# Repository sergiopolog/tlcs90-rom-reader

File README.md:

# TLCS-90 Internal ROM Reader Tool

TLCS-90 ROM Reader is custom made tool intended to read the inner ROM content that TLCS-90 series Toshiba MCUs have internally, at least for the models which support it.

[](img/mcu-nmk215.jpeg)

Devices in the TLCS-90 family from Toshiba are MCUs with a Z80 core and a quite similar instruction set, but they have additional features than the original CPU from Zilog, such us:
  - Internal Counters
  - Wathdog
  - A/D converters
  - Serial port support
  - Stepping motors support
  - and more...
  
There are also devices in the family which have some space reserved for Internal ROM and RAM in their memory map, allowing to have an entire microcomputer system in a single chip (program code and work RAM could be included inside the chip).

## Where it started

Motivation of doing this started some years ago when I sourced a pcb of the GunNail arcade game from NMK (1992) in a very bad condition, including lot of rust and rotten components and traces.
Some the chips included in that pcb were very clearly faulty, with broken legs and serious damage. One of them is labeled as NMK-215, a supposedly custom-chip made by NMK back then with custom behavior, as its name already says.
After some investigation, I realized that component is in fact a Toshiba MCU, because the pinout matches with one of the models of those series as shown on their databook, at least the power pins (Vcc and Ground), reset, clock, address and data buses.
Those types of MCU, as said above, could have internal ROM, where it stores a program to be executed by the MCU itself. And that's probably the case for that NMK board.

Then, the first attempt to read if the internal ROM was in a phisical way. I sent the chip to [Furrtek](http://furrtek.free.fr) a while back to be decapped and, in a luckly chance, the ROM could be optically reed from the die, but there was no luck on that shot. The die reveals no visible ROM area, at least from the top view, ~~and a delayering (quite more complex method) should be performed to check if the ROM area will be visible underneath the top metal layer.~~ -> Thanks to [Travis Goodspeed](https://x.com/travisgoodspeed) for pointing out that TLCS-47 series has _Implant ROM_ (Toshiba most likely used the same technology for newer TLCS-90 series) meaning that the difference between P and N silicon describes the bit and, in fact, it's not optically visible  even after delayering, because they are the exact same color.

So, after that try, the next efforts were spent on trying to find a way to exploit the device and read the contents from outside using some external process,  like the way some other MCU devices were successfully dumped.

And that's how this project started. After 3 diferent revisions of the pcb and software made during the process in order to know how the MCU behaves in different scenarios and many of its features, it works for a good number of devices tested by now.

The internal ROMs dumped from several devices helped in improving and even managing to complete emulation on some games in MAME.

## TLCS-90 Series MCUs

| ROM | RAM | CMOS MASK ROM MCU | CMOS NO ROM | PROM MCU   | RESET PIN | SUPPORTED BY THE READER |
| --- | --- | ----------------- | ----------- | ---------- | --------- | --------- |
|  -  |  -  |  -                | TMP90C041N  |  -         | 22        | (not needed) |
|  -  |  1K |  -                | TMP90C141N  |  -         | 22        | (not needed) |
| 4K  | 128 | TMP90C400N        | TMP90C401N  | TMP90P800N | 35        | YES (using adapter) |
| 8K  | 256 | TMP90C800N        | TMP90C801N  | TMP90P800N | 35        | YES (using adapter) |
| **8K**  | **256** | **TMP90C840AN**       | **TMP90C841AN** | **TMP91P640N** | **22**        | **YES**   |
| 8K  | 256 | TMP90C844AN       | TMP90C845AN | TMP90PH44N | 47        | NO        |
| 16K | 320 | TMP91C642AN       | -           | TMP91P642N | 46        | NO        |
| **16K** | **512** | **TMP91C640N**        | **TMP91C641N**  | **TMP91P640N** | **22**        | **YES**   |
| 16k | 512 | TMP90CH44N        | TMP90CH45N  | TMP90PH44N | 47        | NO        |
| **32K** | **1K**  | **TMP90CM40AN**       | **TMP90C141N**  | **TMP90PM40N** | **22**        | **YES** (not tested yet)  |

**Bold** ones have the same pinout as NMK-215.
Not supported ones have slighty different architecture, lacking of /NMI pin, making the Reader pcb not able to achieve the process.
The 400N and 800N ones are (theoretically) supported but a pinout adapter is needed to use them with Reader PCB. However, that is currently untested yet, as I couldn't source any device of those models to check them out.

The tool consists in a combination of a custom-made pcb, a program code written to be executed on the targeted MCU itself, a PLD and glue logic to make all things work together. The tool runs by itself without needing to attach it to another hardware or so, it only requires to be populated with the proper components and powered it using +5V. 

## DISCLAIMER
Any use of this project is under **your own responsibility**. **You** will be responsible of checking the proper installation and functionality of your board and the compatiblity of the chips **You** will insert into it. By using this project **You** will agree that I cannot be held responsible if it will destroy any of your devices, burn down your house or whatever.

Do **NOT** come to me for hand-holding using this. It is **NOT** a plug-and-play tool, and it is something I created for my own research and use, and I released in case someone might have an use for it.

## Assemble

All components used on the PCB design are "Through-Hole". That makes the assembly easier.

1. Build the pcb using the gerbers located in the [pcb/gerbers](pcb/gerbers) folder.
2. Burn the program code from the binary file located at [src](src) folder into a 27C512 EPROM.
3. Burn the PLD from the jedec file located at [pld](pld) folder into a GAL22V10 device.
4. Install all the components into the pcb. Sockets are recommended at least for MCU, EPROM, EEPROM and PLD devices. There is an interactive, html-based BOM file located at [pcb/bom](pcb/bom) which is useful when populating the board.

## How to use

> **IMPORTANT:** Ensure that device is one of the compatible models marked above before proceeding with the process. If the model is unknown, you can check if it is one of the directly supported models by checking the following things:
> * Pins 1 and 64 should be tied to Vcc in the original pcb where it was installed.
> * Pins 2 and 32 should be tied to GND in the original pcb where it was installed.
> * Pin 55 should be tied to Vcc (or to a pull-up resistor) if it uses internal ROM.
> * Additionally, Pin 21 could be tied to Vcc aswell, indicating that no external interrupt is used. However this doesn't happen always.

First of all, ensure the 28C256 EEPROM is unprotected. This type of device can be protected making that any write performed on the device will be rejected. So, you need to ensure always to "Off Protect" the device before installing it on the board. Don't do any other actions on the EEPROM other than de-protecting it before inserting it in the socket of the reader PCB. (Thanks **kuze** for discovering and testing this)

1. Set the `DSW2` with an initial value of **4** (0100).
2. Select the internal ROM size of the target device using `DSW1`. If device model is unknown, then select 32K option to perform a full read. Perhaps, some space should be discarded after reading process.
3. Set the `/EA` switch to the left position **(ON)** (external mode)
4. Turn the power on. There are two options for powering the board:
	- Via Mini-molex floppy drive connector directly from an ATX PSU or similar. In this case connect only the power connector to `J1` and use the `SW1` **only** to turn on the board. Ensure that left pin is +5V and two middle pins are GND. This is the standard pinout for this kind of connectors.
	- Via Barrel connector (**Tip Positive - Ring Negative!!**) up to 12V from an external PSU. In this case connect only the barrel connector to `J2` and use the `SW2` **only** to turn on the board. (It works fine with 9V and 12V external power supplies, but in case of 12V, installing a heatsink on `U15` - L7805 is highly recommended)
5. Push the `/RESET` button shortly and green LED at `D2` will turn on, marking the PCB is ready.
6. Toggle the `/EA` switch to the right position **(OFF)** (internal mode)
7. Push again the `/RESET` button to start the read process. Green LED turns off.
8. When green LED turns on again, the process ended successfully. Time spent in the read process depends on the MCU model and the size of its internal ROM. A 8K internal ROM takes about 55 seconds, 16K one about 110 seconds and 32K one about 220 seconds using a 4MHz XTAL on the PCB. It could be upgraded up to 10MHz (max freq. allowed by the MCU), in order to reduce those dump times, but that's not really needed.
9. The contents of the internal ROM are written to the EEPROM located at `U3`. Carefully extract it from the socket and read contents with a proper EPROM reader.

If the initial rom size was unknown and the model wasn't really a 32K device, some extra content was read by the process and was placed at the end of the dumped file. In that file could be some flag values at some specific addresses marking what is the real internal ROM size:
* If a **"3B"** value is located at `$2000`, then the internal ROM is only  8K an the content between `$2000 - $8000` in the dump file should be discarded.
* If a **"4B"** value is located at `$4000`, then the internal ROM is only 16K an the content between `$4000 - $8000` in the dump file should be discarded.
* If none of those values are present at those positions, then the dump is really 32K length and no content should be discarded.

> **NOTE:** If the green led doesn't turn on long after those estimated times, then it should be a problem in the read process. Please check the [Special cases](#special-cases) section.

Powering the board using Barrel Connector and an external 9V DC power supply (**Tip Positive!**):  
[](img/Powered_by_Barrel_Connector.jpeg)

## How it works

### TLCS-90 features

The dump method implemented in this tool sits over these features/behaviors of the TCLS-90 MCUs:

* The MCU provides an input pin called `/EA` ("External Access") and when it's asserted (low level), the MCU ignores the internal ROM (and RAM) space and addresess it to the outside using the address port pins. When it's not asserted it uses the internal ROM placed on the beginning of the memory map ($0000 - $2000, $0000 - $4000.. etc, depending of the specific MCU model). So we can externally control if the MCU starts in external or internal mode.
* The `/EA` pin doesn't allow a hot-swap, when the MCU is running, and only sets the value when resetting the device.
* Like a plain Z80 cpu, the first instruction fetched after reset is on `$0000` address. If the internal mode is enabled, that fetch is done from the internal ROM.
* Reset process only clear values for a few registers in the MCU. These are the PC register, AF register pair and IFF flags. The rest of the registers remain unchanged from previous execution (if any), including SP (Stack Pointer)
* When resetting the device in internal mode, the Address pins are set as input port by default, and it should be configured as address pins programatically if desire.
* External interrupt handling is basically the same as a plain Z80, saving PC value and AF value into the stack and restore them after ending interrupt subroutine.

### Exploit

Considering that, this is basically how the dump method works:

1. Start the device in external mode and the program code puts an external address value into the Stack Point register (SP). Then, the program halt the device waiting for reset.
2. Manually toggle the /EA pin to switch to internal mode and then reset again.
3. As SP value remains unchanged after that reset, if any interrupt is asserted, the device will store the PC value and some others into the stack, that is currently now at external zone pointed by the previous SP value
4. Inmediatly right after that second reset is released, the pcb logic generates a pulse into the `/NMI` pin to send an (non-maskable) interrupt. The device doesn't have enough time to fetch firsts instructions at `$0000` (that would probably set the SP to its own value), and it goes to handle the interrupt.
5. Device stores the PC and other values into the stack, that is currently on external zone, but the Address Port is configured as input port right after reset, so it doesn't effectively output the address on the device address pins to store those values, but doesn't care, they will not be used.
6. After running the interrupt subroutine (tipycally, it simply returns the control without doing anything else related to outside), the PC value (and others) need to be returned back from stack, and the device tries to read them from the external zone.
7. The pcb logic, using the `/RD` pin to count each fetch, artificially sends a new convenient PC value, so now the PC in the device is pointing to the zone we want (external zone).
8. The device tries to fetch instruction from the new injected PC address value, but the Address Port still remains as an input port after reset, so it doesn't output the proper address value to fetch the instruction.
9. The pcb logic again, using the `/RD` pin to count the subsequent fetches, artificially sends a sequence of 6 bytes, conforming 2 instructions to be executed by the device. Those instructions were carefully chosen to enable the Address pin to act effectively as an address port (output).
10. Next instruction is fetched normally by the device using the address port on the next PC value, and then we finally gain control of the device.
11. Next step is initiallize the rest of the device registers and ports and run the custom program stored in the external EPROM
12. The MCU itself copies the internal rom content ($0000 to $1FFF, or to $3FFF, or to $7FFF) to the EEPROM (Non-volatile) installed in the PCB by running the program code in the EPROM.

### Attack Timing

Below picture shows the main signals involved in the attack and how they evolve during the attack process:

[](img/tlcs90-attack-timing.jpg)

### Special cases

If the interrupt routine does one or more reads by addressing the external zone, prior to return the control, or it pushes/pops values from the stack during that interrupt subroutine (the stacks pointer still points to the external zone and it provokes writes/reads there), the counter on the PCB will be confused and won't inject the proper values at the proper times. So if the internal code does that, this method will not work with the initial configuration. Anyway, it's rare that the NMI routine does data fetches from the external zone.

In this case, a workaround could be effective. That is trying to locate where the interrupt subroutine ends and what is the first fetch from stack during RETI instruction to take the AF register and then PC register. By adjusting DSW2, substracting some units to the initial configured value, will delay the reads count in order to sync the time when RETI tries to fetch PC value from stack with the time the PCB logic injects it to the data bus (i.e.: 4 -> 2).

Another rare case that could happen is that RET instruction is used instead of RETI when ending the interrupt subroutine. The difference is that RET only does "POP PC" and RETI does both "POP AF" and then "POP PC", so there will be two less read cycles when returning from interrupt. That could be adjusted with the DSW2 by adding two units to the value configured there (i.e.: 4 -> 6) in order to sync the time when PC value is injected in the same way as the previous case.

In all of these rare cases, the way to go is playing with different values on the DSW2, by adding or substracting some units to the value configured in it until syncing the time when the new PC value should be injected.

Obviously, if the interrupt routine does many complex things, a custom solution should be made for attacking that specific device. A Logic Analyzer would be a great help to inspect what happens after the NMI pulse is generated by the reader PCB logic.

In a weird case, I discovered that one program has a direct jump on the interrupt subroutine, instead of the RETI instruction. In that case, the program jumped to remote program address (inside internal ROM) and continue executing instructions, until it calls to a subroutine. In that moment the value of the PC was stored in the stack (still pointing to external zone) and when the subroutine ended, the program tried to take the PC value back from the stack and at that point the new PC value was injected. In all of that execution time, no external fetches were done, so the first one was for returing back that PC value, and the new one was injected.

## Known TLCS-90 based devices

Below there is a table with the current known devices based on TLCS-90 series MCUs, model, features and if the contents are currently dumped, aswell.

|  Device Ref.  |  Device Model  |  Package  |  Dev. Company  |  Found on Hw  |  Dumped?  |  Config. used to dump (DSW2)  | Picture |
| --- | --- | ----------------- | ----------------- | ----------- | ----------- | ----------- | ----------- |
|  NMK-004  |  TMP90840  |  QFP64  |  NMK  |  many NMK games (sound cpu)  |  [**Yes**](https://github.com/mamedev/mame/blob/0006fba49565386afa9b66d9fb8e02f744cf7cdb/src/mame/nmk/nmk004.cpp#L83)<br/>(using [trap15 method](http://daifukkat.su/blog/archives/2014/09/13/nmk004_rom_dumping_part_5_the_release/))<br/>Also dumped using **TLCS90-ROM-Reader** and adapter located at [adapter/tmp90c840-qfc2sdip](adapter/tmp90c840-qfc2sdip)  |  2  |  [Link](img/mcu-nmk004.jpeg)  |
|  NMK-110  |  TMP91640  |  SDIP64  |  NMK  |  ddealer & tdragon<br/>(different internal ROM on each one)  |  [**Yes**](https://github.com/mamedev/mame/blob/0006fba49565386afa9b66d9fb8e02f744cf7cdb/src/mame/nmk/ddealer.cpp#L463)  and  [**Yes**](https://github.com/mamedev/mame/blob/0006fba49565386afa9b66d9fb8e02f744cf7cdb/src/mame/nmk/nmk16.cpp#L6447)  |  4  |  [Link](img/mcu-nmk110.jpeg)  |
|  NMK-113  |  TMP91640  |  SDIP64  |  NMK  |  hachamf  |  [**Yes**](https://github.com/mamedev/mame/blob/0006fba49565386afa9b66d9fb8e02f744cf7cdb/src/mame/nmk/nmk16.cpp#L6801)  |  4  |  [Link](img/mcu-nmk113.jpeg)   |
|  NMK-215  |  TMP90840  |  SDIP64  |  NMK  |  sabotenb, bjtwin, macross, gunnail  |  [**Yes**](https://github.com/mamedev/mame/blob/0006fba49565386afa9b66d9fb8e02f744cf7cdb/src/mame/nmk/nmk16.cpp#L7480)  |  4  |  [Link](img/mcu-nmk215.jpeg)   |
|  -  |  TMP90840  |  SDIP64  |  Dynax  |  mjvegas  |  [**Yes**](https://github.com/mamedev/mame/blob/26072bb747281a3abb519dc2a2c38884b9c5d479/src/mame/dynax/royalmah.cpp#L5159)  |  2  |  [Link](img/mcu-mjvegas.jpeg)   |
|  -  |  TMP90840  |  SDIP64  |  Dynax  |  cafedoll  |  [**Yes**](https://github.com/mamedev/mame/blob/26072bb747281a3abb519dc2a2c38884b9c5d479/src/mame/dynax/royalmah.cpp#L5042)  |  2  |  [Link](img/mcu-cafedoll.jpeg)  |
|  -  |  TMP90840  |  SDIP64  |  Dynax  |  cafetime  |  [**Yes**](https://github.com/mamedev/mame/blob/26072bb747281a3abb519dc2a2c38884b9c5d479/src/mame/dynax/royalmah.cpp#L98)  |  2  |  [Link](img/mcu-cafetime.jpeg)  |
|  -  |  TMP91640  |  SDIP64  |  Dynax  |  cafebrk  |  [**Yes**](https://github.com/mamedev/mame/blob/26072bb747281a3abb519dc2a2c38884b9c5d479/src/mame/dynax/royalmah.cpp#L5340)  |  2  |  [Link](img/mcu-cafebrk.jpeg)  |
|  -  |  TMP91640  |  SDIP64  |  Dynax  |  cafepara |  [**Yes**](https://github.com/mamedev/mame/blob/26072bb747281a3abb519dc2a2c38884b9c5d479/src/mame/dynax/royalmah.cpp#L5072)  |  2  |  [Link](img/mcu-cafepara.jpeg)  |
|  -  |  TMP90840  |  SDIP64  |  Dynax  |  mjtensin  |  [**Yes**](https://github.com/mamedev/mame/blob/fe923e9b3c464d7e373dd1992c6001b47b572e19/src/mame/dynax/royalmah.cpp#L4868)<br/>*(not used by the game code)*  |  4  |  [Link](img/mcu-mjtensin.jpeg)  |
|  -  |  TMP91640  |  SDIP64  |  Dynax  |  majrjh  |  [**Yes**](https://github.com/mamedev/mame/blob/000c31fae55296ae3a853f2ffbe44a6d46dc7a3a/src/mame/dynax/royalmah.cpp#L4970)  |  2  |  [Link](img/mcu-majrjhdx.jpeg)  |
|  -  |  TMP91640  |  SDIP64  |  Dynax  |  majrjhdx  |  [**Yes**](https://github.com/mamedev/mame/blob/000c31fae55296ae3a853f2ffbe44a6d46dc7a3a/src/mame/dynax/royalmah.cpp#L4955)<br/>*(same dump as majrjh)*  |  2  |  [Link](img/mcu-majrjhdx.jpeg)  |
|  -  |  ?  |  SDIP64  |  Dynax  |  gekisha  |  No  |  -  |  -  |
|  -  |  TMP91640  |  SDIP64  |  Dynax  |  tenkai  |  [**Yes**](https://github.com/mamedev/mame/blob/88a47305a4a5987fbe0e9160d8dd6b6a9c3a2314/src/mame/dynax/dynax.cpp#L6820)<br/>*(already dumped previosly)*<br/>*(pending to be dumped using this method)*  |  -  |  -  |
|  -  |  ?  |  SDIP64  |  Dynax  |  tenkai2b  |  No  |  -  |  -  |
|  -  |  TMP90840  |  SDIP64  |  Dynax  |  ougonhai  |  [**Yes**](https://github.com/mamedev/mame/blob/fe923e9b3c464d7e373dd1992c6001b47b572e19/src/mame/dynax/dynax.cpp#L7021)  |  2  |  [Link](img/mcu-ougonhai.jpeg)   |
|  -  |  TMP90840  |  SDIP64  |  Dynax  |  mjreach  |  [**Yes**](https://github.com/mamedev/mame/blob/fe923e9b3c464d7e373dd1992c6001b47b572e19/src/mame/dynax/dynax.cpp#L6662)  |  2  |  [Link](img/mcu-mjreach.jpeg)   |
|  -  |  TMP90840  |  SDIP64  |  Dynax  |  mjreach2  |  [**Yes**](https://github.com/mamedev/mame/blob/3f9d6b905f18b8800a9420abdd981ee51502d85e/src/mame/dynax/dynax.cpp#L6751)  |  2  |  [Link](img/mcu-mjreach2.jpeg)   |
|  -  |  ?  |  SDIP64  |  Jaleco  |  avspirit  |  No  |  -  |  -  |
|  -  |  TMP91640  |  SDIP64  |  Jaleco  |  edf  |  [**Yes**](https://github.com/mamedev/mame/blob/df3e2de8e1815f0c22419c298471fbb8776858a2/src/mame/jaleco/megasys1.cpp#L3145)<br/>Thanks to **Darren Olafson**<br/>Double checked by *me*.  |  6  |  [Link](img/mcu-edf.jpeg)  |
|  MO-91009  |  TMP91640  |  SDIP64  |  Jaleco  |  64street  |  [**Yes**](https://github.com/mamedev/mame/blob/7b047641fe763667882a8c3320ad24163c63d327/src/mame/jaleco/megasys1.cpp#L2297)  |  6  |  [Link](img/mcu-mo91009.jpeg)  |
|  MO-91021  |  TMP91640  |  SDIP64  |  Jaleco  |  bigstrik  |  [**Yes**](https://github.com/mamedev/mame/blob/7b047641fe763667882a8c3320ad24163c63d327/src/mame/jaleco/megasys1.cpp#L2879)  |  6  |  [Link](img/mcu-mo91021.jpeg)  |
|  MO-91028  |  TMP91640  |  SDIP64  |  Jaleco  |  chimerab |   [**Yes**](https://github.com/mamedev/mame/blob/7b047641fe763667882a8c3320ad24163c63d327/src/mame/jaleco/megasys1.cpp#L2927)<br/>*(same dump as cybattlr)*<br/>Thanks to **kuze**  |  6  |  [Link](img/mcu-mo91028.jpeg)  |
|  -  |  ?  |  SDIP64  |  Jaleco  |  chimeraba |  No  |  -  |  -  |
|  MO-91028  |  TMP91640  |  SDIP64  |  Jaleco  |  cybattlr  |   [**Yes**](https://github.com/mamedev/mame/blob/7b047641fe763667882a8c3320ad24163c63d327/src/mame/jaleco/megasys1.cpp#L3049)<br/>Thanks to **kuze**  |  6  |  [Link](img/mcu-mo91028.jpeg)  |
|  MO-91044  |  ?  |  SDIP64  |  Jaleco  |  hayaosi1  |  No  |  -  |  -  |
|  MO-92033  |  TMP91640  |  SDIP64  |  Jaleco  |  peekaboo  |  [**Yes**](https://github.com/mamedev/mame/blob/225c0586cb9f0f3c8fb234736ba2863dffa12c69/src/mame/jaleco/megasys1.cpp#L4424)  |  4  |  [Link](img/mcu-mo92033.jpeg)  |
|  -  |  TMP90840  |  QFP64  |  Toshiba  |  T1600 Laptop PSU  |  [**Yes**](bin/mcu-t1600psu.bin)<br/>Using adapter located at [adapter/tmp90c840-qfc2sdip](adapter/tmp90c840-qfc2sdip)  |  4  |  [Link](img/mcu-t1600psu.jpeg)  |

If you find more devices based on this MCU series, have additional info or successfully dump some, please let me know to add them to the above table, just as reference. 

## Prototypes and previous versions

During the process some previous versions of the board was manufactured and tested, in order to understand the behaviour of the MCU in some special cases and test different attacks over it. 

### Version 1 (Proto - Test board)

This board was the first ever made and the purpose of that was testing the behaviour of the TLCS90 devices and perform some simple attack attempts and see how the device behaves under them.

[](img/TLCS90-rom-reader-v1.jpg)

### Version 2 (Proto - Attack board)

Using the data compiled from the first version, the second one includes the implementation of the main attack with some small variants to be tested with real devices.

[](img/TLCS90-rom-reader-v2-front.jpg)

Multiple patches needed to be done directly in the pcb in order to fix errors and test slight variations of the attack :D

[](img/TLCS90-rom-reader-v2-back.jpeg)

### Version 3 (Final version)

After confirming the attack is successfull for several devices, the unused parts were removed and the layout was simplified. Added support for selecting the type of device (by its internal ROM size). Also an additional option to power the board via barrel connector was added. 

[](img/mcu-nmk215.jpeg)

## Special Thanks

Special thanks to  [hammy](https://www.youtube.com/@HammyArcade) for his valuable help on the research of this project and helping in sourcing PCBs and TLCS90 devices for testing.

## Contact

[@Recre_Piscis](https://x.com/Recre_Piscis) on X (_Twitter_).

## License

See [LICENSE](LICENSE) for more details.

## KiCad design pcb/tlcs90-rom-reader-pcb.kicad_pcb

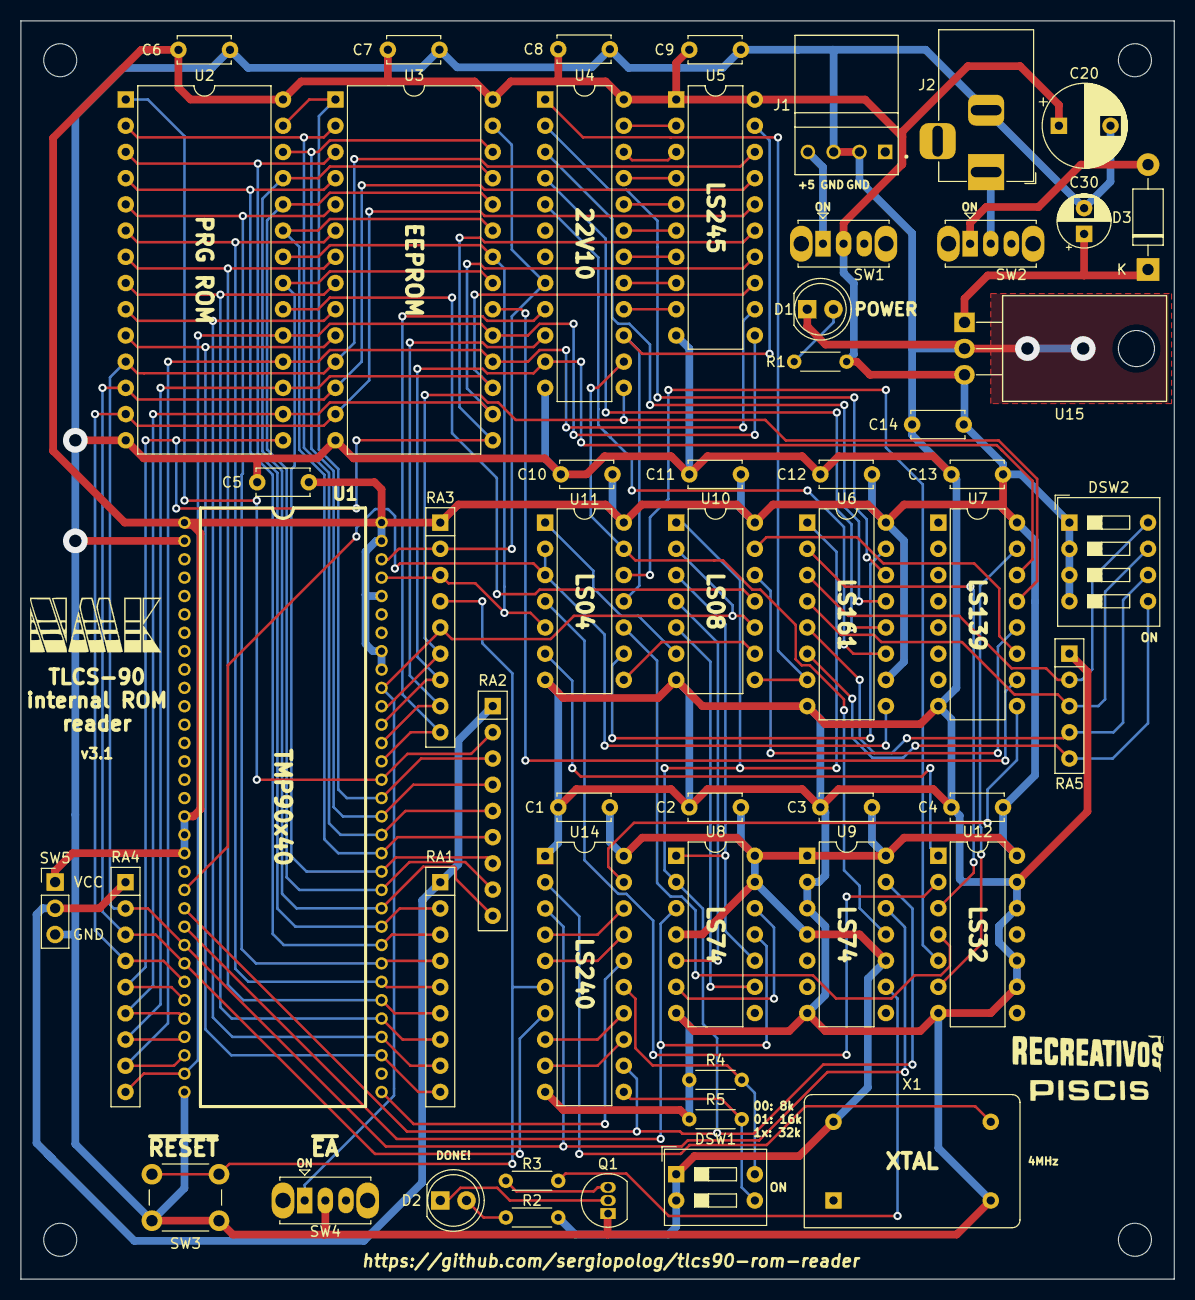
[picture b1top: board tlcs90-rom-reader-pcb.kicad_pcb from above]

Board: 2 copper layers, 111.8 x 121.9 mm, 60 parts (0 on the bottom side), 92 nets.

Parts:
C1, C2, C3, C4, C5, C6, C7, C8, C9, C10, C11, C12, C13, C14: 0.1; C_Disc_D5.0mm_W2.5mm_P5.00mm
C20: 470u 16V; CP_Radial_D8.0mm_P5.00mm
C30: 0.22; CP_Radial_D5.0mm_P2.50mm
D1: RED LED; LED_D5.0mm
D2: GREEN LED; LED_D5.0mm
D3: 1N4001; D_DO-41_SOD81_P10.16mm_Horizontal
DSW1: SW_DIP_x02; SW_DIP_SPSTx02_Slide_9.78x7.26mm_W7.62mm_P2.54mm
DSW2: SW_DIP_x04; SW_DIP_SPSTx04_Slide_9.78x12.34mm_W7.62mm_P2.54mm
H1, H2, H3, H4: MountingHole; MountingHole_3.2mm_M3
J1: Conn_01x04; TE_171826-4
J2: Conn_Coaxial_Power; BarrelJack_Horizontal
L1: RECRE-PISCIS-LOGO-10mm; recre_piscis_logo
L2: NMK-LOGO; nmk-logo
Q1: Q_NPN_ECB; TO-92_Inline
R1, R3: 4.7K; R_Axial_DIN0204_L3.6mm_D1.6mm_P5.08mm_Horizontal
R2: 330; R_Axial_DIN0204_L3.6mm_D1.6mm_P5.08mm_Horizontal
R4, R5: 10K; R_Axial_DIN0204_L3.6mm_D1.6mm_P5.08mm_Horizontal
RA1, RA2, RA3, RA4: 10K; R_Array_SIP9
RA5: 10K; R_Array_SIP5
SW1, SW2, SW4: SW_SPDT; SW_Slide_1P2T_CK_OS102011MS2Q
SW3: SW_Push; SW_PUSH_6mm
SW5: PinHeader; PinHeader_1x03_P2.54mm_Vertical
U1: TMP90C840AN; SDIP-64_W19.05mm
U2: 27C512; DIP-28_W15.24mm
U3: 28C256; DIP-28_W15.24mm
U4: GAL22V10; DIP-24_W7.62mm
U5: 74LS245; DIP-20_W7.62mm
U6: 74LS161; DIP-16_W7.62mm
U7: 74LS139; DIP-16_W7.62mm
U8, U9: 74LS74; DIP-14_W7.62mm
U10: 74LS08; DIP-14_W7.62mm
U11: 74LS04; DIP-14_W7.62mm
U12: 74LS32; DIP-14_W7.62mm
U14: 74LS240_Split; DIP-20_W7.62mm
U15: L7805; TO-220-3_Horizontal_TabDown
X1: 4MHz; Oscillator_DIP-14

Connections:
+12V: C30.1, D3.1, U15.1
/IN12V: J2.1, SW2.2
/SW12V: D3.2, SW2.1
A0: RA1.9, U1.35, U2.10, U3.10
A1: RA1.8, U1.36, U2.9, U3.9
A2: RA1.7, U1.37, U2.8, U3.8
A3: RA1.6, U1.38, U2.7, U3.7
A4: RA1.5, U1.39, U2.6, U3.6
A5: RA1.4, U1.40, U2.5, U3.5
A6: RA1.3, U1.41, U2.4, U3.4
A7: RA1.2, U1.42, U2.3, U3.3
A8: RA2.9, U1.43, U2.25, U3.25
A9: RA2.8, U1.44, U2.24, U3.24
A10: RA2.7, U1.45, U2.21, U3.21
A11: RA2.6, U1.46, U2.23, U3.23
A12: RA2.5, U1.47, U2.2, U3.2
A13: RA2.4, U1.48, U2.26, U3.26
A14: RA2.3, U1.49, U2.27, U3.1
A15: RA2.2, U1.50, U2.1
A16: RA3.9, U1.51, U4.9
A17: RA3.8, U1.52, U4.10
A18: RA3.7, U1.53, U4.11, U7.14
A19: RA3.6, U1.54, U4.13, U7.13
C0: U4.2, U6.14
C1: U4.3, U6.13
C2: U4.4, U6.12
C3: U4.5, U6.11
CLK: U1.23, U8.3, U8.11
D0: RA4.2, U1.24, U2.11, U3.11, U5.18, U9.12, U14.3
D1: RA4.3, U1.25, U2.12, U3.12, U5.17, U14.7
D2: RA4.4, U1.26, U2.13, U3.13, U5.16
D3: RA4.5, U1.27, U2.15, U3.15, U5.15
D4: RA4.6, U1.28, U2.16, U3.16, U5.14
D5: RA4.7, U1.29, U2.17, U3.17, U5.13
D6: RA4.8, U1.30, U2.18, U3.18, U5.12
D7: RA4.9, U1.31, U2.19, U3.19, U5.11
GND: C1.2, C2.2, C3.2, C4.2, C5.2, C6.2, C7.2, C8.2, C9.2, C10.2, C11.2, C12.2, C13.2, C14.2, C20.2, C30.2, D1.1, J1.2, J1.3, J2.2, Q1.1, R4.2, R5.2, RA5.1, SW3.2, SW4.2, SW5.3, U1.2, U1.32, U2.14, U3.14, U4.12, U5.10, U6.8, U7.8, U8.7, U9.2, U9.3, U9.7, U10.7, U11.7, U12.7, U12.9, U12.10, U12.12, U12.13, U14.1, U14.10, U15.2, X1.7
NMI-RESET-POS: U11.4, U12.2
unnamed: D1.2, R1.1
unnamed: D2.1, Q1.2
unnamed: D2.2, R2.1
unnamed: DSW1.3, R5.1, U14.11
unnamed: DSW1.4, R4.1, U14.15
unnamed: DSW2.5, RA5.5, U6.6
unnamed: DSW2.6, RA5.4, U6.5
unnamed: DSW2.7, RA5.3, U6.4
unnamed: DSW2.8, RA5.2, U6.3
unnamed: J1.4, SW1.1
unnamed: Q1.3, R3.1
unnamed: R3.2, U9.9
unnamed: RA1.1, RA2.1, RA4.1, SW5.2
unnamed: RA3.4, SW3.1, U14.6
unnamed: U1.33, U14.16
unnamed: U4.16, U5.9
unnamed: U4.17, U5.8
unnamed: U4.18, U5.7
unnamed: U4.19, U5.6
unnamed: U4.20, U5.5
unnamed: U4.21, U5.4
unnamed: U4.22, U5.3
unnamed: U4.23, U5.2
unnamed: U8.6, U8.12
unnamed: U8.1, U8.10, U10.3
unnamed: U8.5, U10.4
unnamed: U8.9, U10.5
unnamed: U10.6, U11.1
unnamed: U10.9, U11.8
unnamed: U7.12, U10.12
unnamed: U7.11, U10.13
unnamed: U11.6, U12.1
unnamed: U6.15, U11.9
unnamed: U11.10, U12.4
unnamed: U4.15, U5.19, U11.11
unnamed: U11.12, U12.5
unnamed: U4.14, U9.11, U11.13
unnamed: U6.2, U12.3
unnamed: U7.15, U12.6
unnamed: U14.2, X1.8
unnamed: U14.9, U14.13
unnamed: U14.8, U14.14
unnamed: U14.5, U14.17
unnamed: U14.4, U14.18
VCC: C1.1, C2.1, C3.1, C4.1, C5.1, C6.1, C7.1, C8.1, C9.1, C10.1, C11.1, C12.1, C13.1, C14.1, C20.1, DSW1.1, DSW1.2, DSW2.1, DSW2.2, DSW2.3, DSW2.4, R1.2, R2.2, RA3.1, SW1.2, SW5.1, U1.1, U1.17, U1.18, U1.19, U1.56, U1.57, U1.60, U1.63, U1.64, U2.28, U3.28, U4.24, U5.1, U5.20, U6.10, U6.16, U7.16, U8.4, U8.13, U8.14, U9.1, U9.4, U9.10, U9.14, U10.14, U11.14, U12.14, U14.20, U15.3, X1.14
~DISABLE-COUNT: U4.1, U6.7, U10.8
~DSW-ENABLE: U7.9, U14.19
~EA: RA3.5, SW4.1, U1.55, U10.2, U10.10
~EEPROM-ENABLE: U3.20, U7.10
~NMI-RESET: U1.21, U6.9, U11.2, U11.3
~RD: RA3.3, U1.61, U2.22, U3.22, U11.5
~RESET: U1.22, U6.1, U8.2, U9.13, U10.1, U14.12
~ROM-ENABLE: U2.20, U10.11
~WR: RA3.2, U1.62, U3.27, U4.8

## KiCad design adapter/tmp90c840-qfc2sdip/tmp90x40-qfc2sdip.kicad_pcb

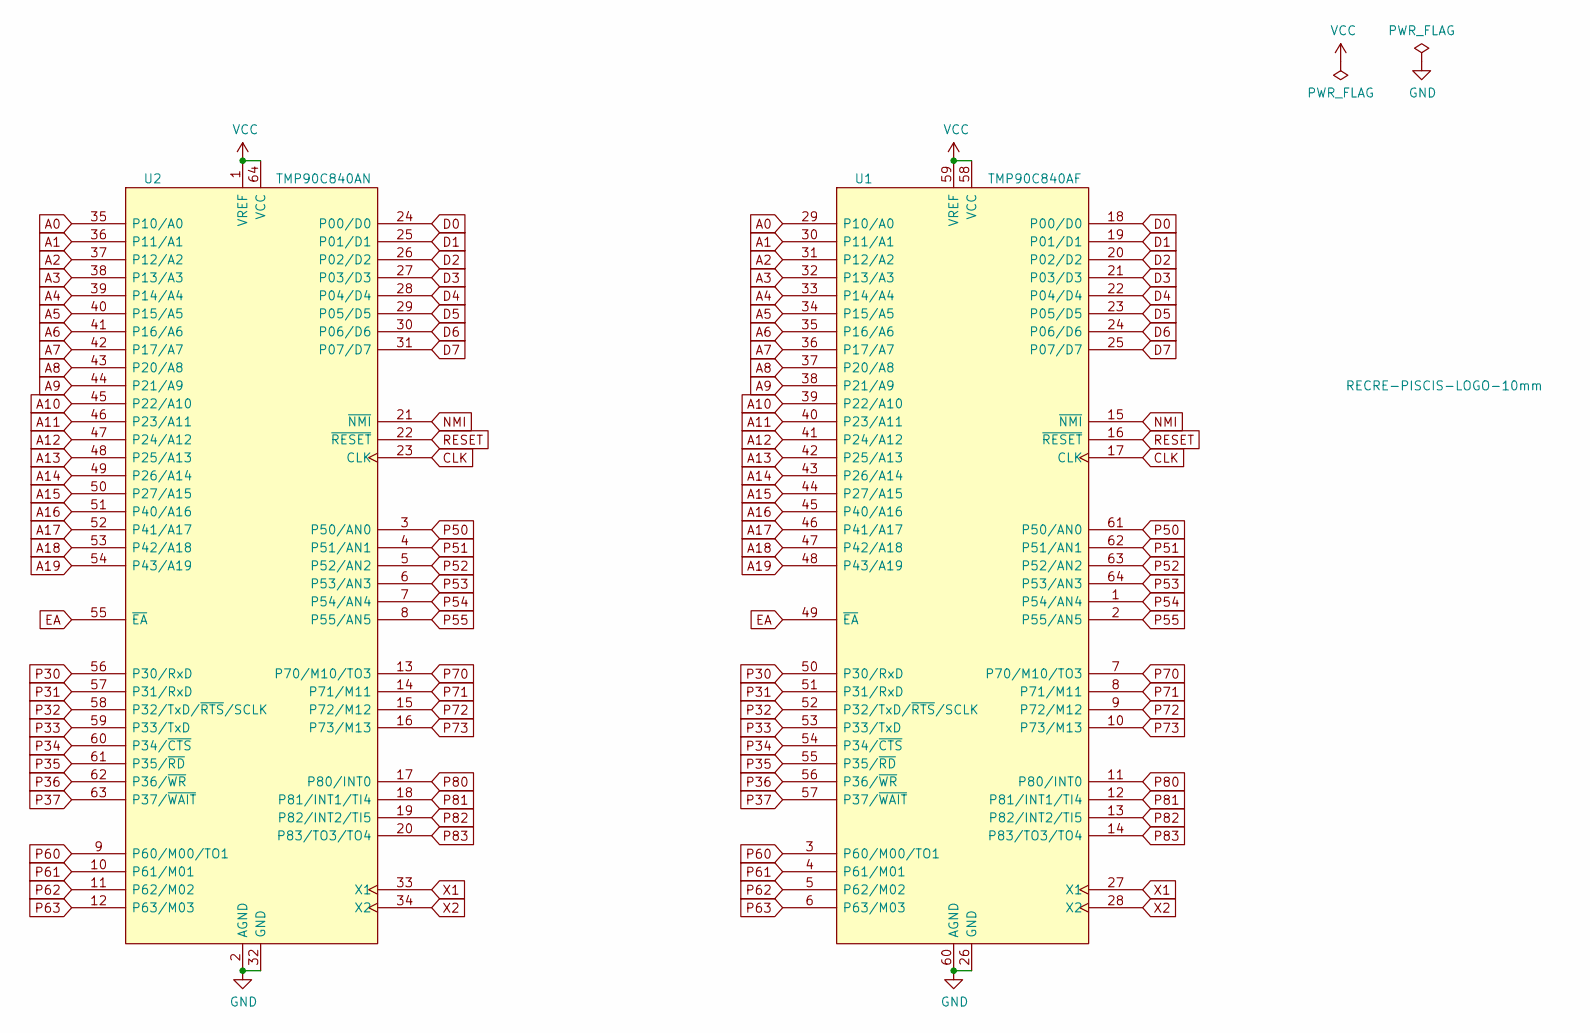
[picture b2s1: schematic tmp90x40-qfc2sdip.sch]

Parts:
L1: RECRE-PISCIS-LOGO-10mm; recre_piscis_10mm
U1: TMP90C840AF; PQFP-64_20x14mm_P1mm
U2: TMP90C840AN; SDIP-64_W19.05mm_no_silk

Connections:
A0: U1.29 (P10/A0), U2.35 (P10/A0)
A1: U1.30 (P11/A1), U2.36 (P11/A1)
A2: U1.31 (P12/A2), U2.37 (P12/A2)
A3: U1.32 (P13/A3), U2.38 (P13/A3)
A4: U1.33 (P14/A4), U2.39 (P14/A4)
A5: U1.34 (P15/A5), U2.40 (P15/A5)
A6: U1.35 (P16/A6), U2.41 (P16/A6)
A7: U1.36 (P17/A7), U2.42 (P17/A7)
A8: U1.37 (P20/A8), U2.43 (P20/A8)
A9: U1.38 (P21/A9), U2.44 (P21/A9)
A10: U1.39 (P22/A10), U2.45 (P22/A10)
A11: U1.40 (P23/A11), U2.46 (P23/A11)
A12: U1.41 (P24/A12), U2.47 (P24/A12)
A13: U1.42 (P25/A13), U2.48 (P25/A13)
A14: U1.43 (P26/A14), U2.49 (P26/A14)
A15: U1.44 (P27/A15), U2.50 (P27/A15)
A16: U1.45 (P40/A16), U2.51 (P40/A16)
A17: U1.46 (P41/A17), U2.52 (P41/A17)
A18: U1.47 (P42/A18), U2.53 (P42/A18)
A19: U1.48 (P43/A19), U2.54 (P43/A19)
CLK: U1.17 (CLK), U2.23 (CLK)
D0: U1.18 (P00/D0), U2.24 (P00/D0)
D1: U1.19 (P01/D1), U2.25 (P01/D1)
D2: U1.20 (P02/D2), U2.26 (P02/D2)
D3: U1.21 (P03/D3), U2.27 (P03/D3)
D4: U1.22 (P04/D4), U2.28 (P04/D4)
D5: U1.23 (P05/D5), U2.29 (P05/D5)
D6: U1.24 (P06/D6), U2.30 (P06/D6)
D7: U1.25 (P07/D7), U2.31 (P07/D7)
EA: U1.49 (~EA), U2.55 (~EA)
GND: U1.26 (GND), U1.60 (AGND), U2.2 (AGND), U2.32 (GND)
NMI: U1.15 (~NMI), U2.21 (~NMI)
P30: U1.50 (P30/RxD), U2.56 (P30/RxD)
P31: U1.51 (P31/RxD), U2.57 (P31/RxD)
P32: U1.52 (P32/TxD/~RTS~/SCLK), U2.58 (P32/TxD/~RTS~/SCLK)
P33: U1.53 (P33/TxD), U2.59 (P33/TxD)
P34: U1.54 (P34/~CTS), U2.60 (P34/~CTS)
P35: U1.55 (P35/~RD), U2.61 (P35/~RD)
P36: U1.56 (P36/~WR), U2.62 (P36/~WR)
P37: U1.57 (P37/~WAIT), U2.63 (P37/~WAIT)
P50: U1.61 (P50/AN0), U2.3 (P50/AN0)
P51: U1.62 (P51/AN1), U2.4 (P51/AN1)
P52: U1.63 (P52/AN2), U2.5 (P52/AN2)
P53: U1.64 (P53/AN3), U2.6 (P53/AN3)
P54: U1.1 (P54/AN4), U2.7 (P54/AN4)
P55: U1.2 (P55/AN5), U2.8 (P55/AN5)
P60: U1.3 (P60/M00/TO1), U2.9 (P60/M00/TO1)
P61: U1.4 (P61/M01), U2.10 (P61/M01)
P62: U1.5 (P62/M02), U2.11 (P62/M02)
P63: U1.6 (P63/M03), U2.12 (P63/M03)
P70: U1.7 (P70/M10/TO3), U2.13 (P70/M10/TO3)
P71: U1.8 (P71/M11), U2.14 (P71/M11)
P72: U1.9 (P72/M12), U2.15 (P72/M12)
P73: U1.10 (P73/M13), U2.16 (P73/M13)
P80: U1.11 (P80/INT0), U2.17 (P80/INT0)
P81: U1.12 (P81/INT1/TI4), U2.18 (P81/INT1/TI4)
P82: U1.13 (P82/INT2/TI5), U2.19 (P82/INT2/TI5)
P83: U1.14 (P83/TO3/TO4), U2.20 (P83/TO3/TO4)
RESET: U1.16 (~RESET), U2.22 (~RESET)
VCC: U1.58 (VCC), U1.59 (VREF), U2.1 (VREF), U2.64 (VCC)
X1: U1.27 (X1), U2.33 (X1)
X2: U1.28 (X2), U2.34 (X2)

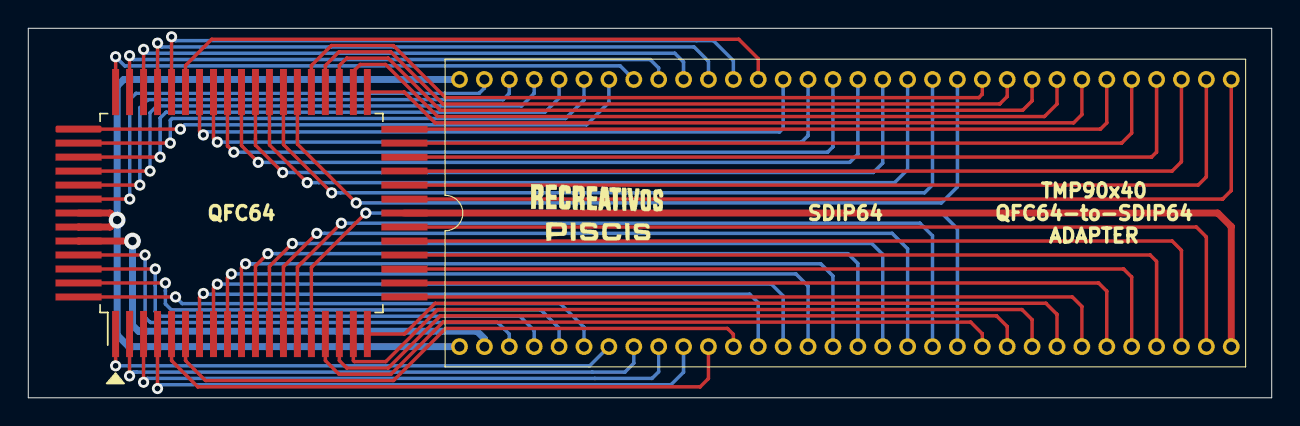
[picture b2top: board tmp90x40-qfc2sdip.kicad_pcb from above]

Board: 2 copper layers, 88.9 x 26.4 mm, 3 parts (0 on the bottom side), 62 nets.

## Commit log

2023-10-28 fix readme
2023-10-28 fix pld readme
2023-11-04 Update README: added notes about Implant ROM
2023-11-21 added info for new MCU dumps
2023-12-10 added dump for majrjhdx
2023-12-10 added majrjh
2024-03-06 added dump for cybattlr and chimerab
2024-03-27 updated dumps for mjreach, mjtensin and ougonhai
2024-03-27 fix picture file extension
2024-04-23 updated dumps for mjreach2
2024-07-01 Added adapter QFP64 to SDIP64 and notes about nmk004
2024-12-11 Added dump for EDF
2025-10-06 Added MO-92033 and T1600 PSU dumps
2025-11-04 new 3.1: added pull-up resistors to /RD and /WR signals
2025-11-05 update pcb: add selector to set Pull-up or Pull-down resistors on address and data buses

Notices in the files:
README.md:
License:
See [LICENSE](LICENSE) for more details.
